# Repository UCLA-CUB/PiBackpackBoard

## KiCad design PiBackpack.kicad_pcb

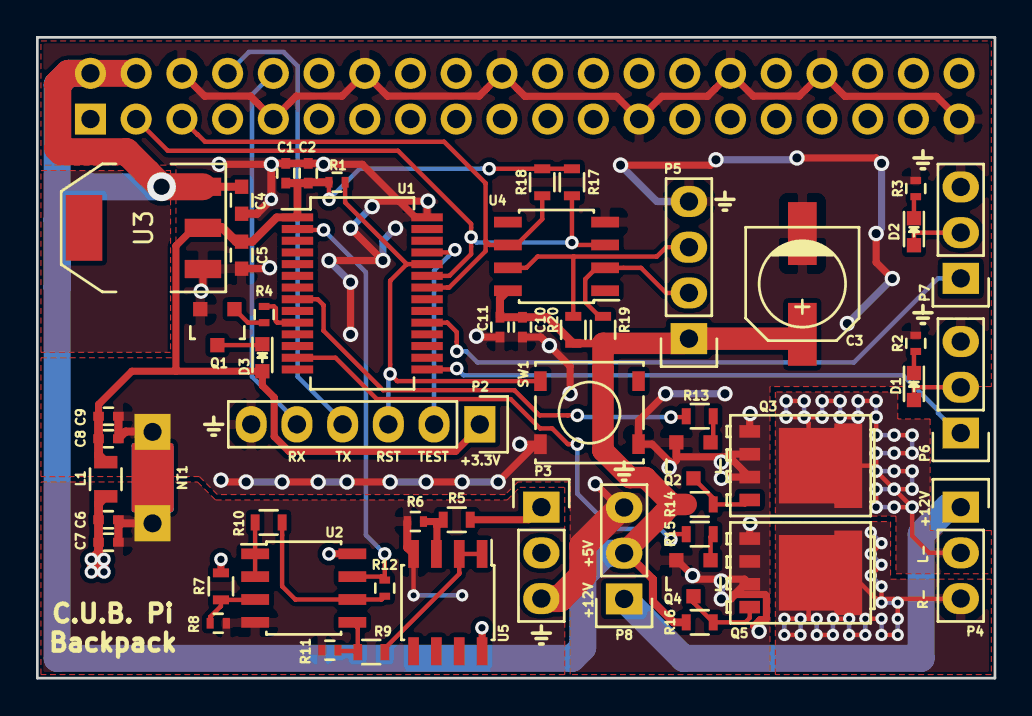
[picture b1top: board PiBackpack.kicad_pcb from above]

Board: 2 copper layers, 53.2 x 35.6 mm, 55 parts (1 on the bottom side), 39 nets.

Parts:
C1, C8, C10: 0.001uF; C_0402
C2, C9, C11: 0.1uF; C_0402
C3: 100uF; c_elec_3.5x5.6
C4, C5: 4.7uF; C_0603
C6: 0.22uF; C_0402
C7: 0.01uF; C_0402
D1, D2: RED LED; LED_0603
D3: GREEN LED; LED_0603
L1: 100uH; R_0805
NT1: NET-TIE_07Mar2012; NetTie-I_Connected
P1: CONN_02X20; Socket_Strip_Straight_2x20
P2: CONN_01X06; Pin_Header_Straight_1x06
P3, P4, P6, P7, P8: CONN_01X03; Pin_Header_Straight_1x03
P5: CONN_01X04; Pin_Header_Straight_1x04
Q1, Q2, Q4: Q_NPN_BEC; SOT-23
Q3, Q5: Q_NMOS_SSSGD; SOT-669_LFPAK
R1: 47K; R_0402
R2, R3: 100R; R_0402
R4: 27K; R_0402
R5: 11K; R_0603
R6: 1.5K; R_0402
R7: 4.3K; R_0603
R8: 7.5K; R_0402
R9, R10: 5.1K; R_0603
R11, R12: 15K; R_0402
R13, R15: 1K; R_0603
R14, R16, R17, R18, R19, R20: 2.2K; R_0603
SW1: SW_PUSH; SW_SPST_TL3315
U1: MSP430G2433IPW28; SSOP-28_5.3x10.2mm_Pitch0.65mm
U2, U5: LM358; SOIC-8_3.9x4.9mm_Pitch1.27mm
U3: AP2114H; SOT-223
U4: P82B715; SOIC-8_3.9x4.9mm_Pitch1.27mm

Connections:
+3.3VADC: C6.1, C7.1, L1.2, R7.1, U2.8, U5.8
+3V3: C1.1, C2.1, C5.1, C8.1, C9.1, D3.2, L1.1, P2.1, R1.1, R17.1, R18.1, U1.1, U3.2
+5V: C3.1, C4.1, C10.1, C11.1, P1.2, P1.4, P5.1, P8.2, R14.1, R16.1, R19.1, R20.1, U3.3, U4.8
+12V: P4.1, P8.1
GND: C1.2, C2.2, C3.2, C4.2, C5.2, C8.2, C9.2, C10.2, C11.2, NT1.2, P1.6, P1.9, P1.14, P1.20, P1.25, P1.30, P1.34, P1.39, P2.6, P3.3, P5.4, P6.3, P7.3, P8.3, Q1.2, Q2.2, Q3.1, Q3.2, Q3.3, Q4.2, Q5.1, Q5.2, Q5.3, R2.2, R3.2, SW1.2, U1.28, U3.1, U4.4
GNDA: C6.2, C7.2, NT1.1, R6.2, R8.2, R11.1, U2.4, U5.4
L_HLIGHT_M: P4.2, Q3.5
L_HLIGHT_SIG: R13.2, U1.8
L_MOT_PLED: D1.2, P6.2
L_MOT_SIG: P6.1, U1.15
Lx_LDA: P5.2, R19.2, U4.2
Ly_LCL: P5.3, R20.2, U4.7
MSP_HB_LED: R4.1, U1.10
MSP_RST: P2.3, R1.2, SW1.1, U1.24
MSP_SCL: P1.5, R18.2, U1.22, U4.6
MSP_SDA: P1.3, R17.2, U1.23, U4.3
MSP_TEST: P2.2, U1.25
unnamed: D1.1, R2.1
unnamed: D2.1, R3.1
unnamed: D3.1, Q1.3
unnamed: Q1.1, R4.2
unnamed: Q2.1, R13.1
unnamed: Q2.3, Q3.4, R14.2
unnamed: Q4.1, R15.1
unnamed: Q4.3, Q5.4, R16.2
unnamed: R10.1, R12.2, U2.6
unnamed: R9.1, R11.2, U2.5
PI_RX: P1.10, P2.5
PI_TX: P1.8, P2.4
R_HLIGHT_M: P4.3, Q5.5
R_HLIGHT_SIG: R15.2, U1.13
R_MOT_PLED: D2.2, P7.2
R_MOT_SIG: P7.1, U1.19
VBAT_SENSE: R12.1, U1.2, U2.7
V_SBAT_24: P3.1, R5.1
V_SBAT_DIV: R5.2, R6.1, U5.3
V_SBAT_DIV_BUF: R9.2, U5.1, U5.2
V_SBAT_DREF: R7.2, R8.1, U2.3
V_SBAT_DREF_BUF: R10.2, U2.1, U2.2

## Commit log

2018-02-01 Added BOM generator and via fixer (resizes vias to minimum size for OSHPark)
